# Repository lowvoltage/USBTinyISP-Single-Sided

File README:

Single-sided PCB version of the USBTinyISP v.2.0 AVR programmer

Original USBTinyISP v.2.0 design: LadyAda @ http://www.ladyada.net/make/usbtinyisp/
Original Single-sided PCB design: Jim Qode @ http://www.symbolengine.com/index.php/usbtinyisp-single-side-board-version/

Author: Dimitar Kovachev, http://lowvoltage.wordpress.com/

Released under the Creative Commons Attribution Share-Alike 3.0 license
http://creativecommons.org/licenses/by-sa/3.0/

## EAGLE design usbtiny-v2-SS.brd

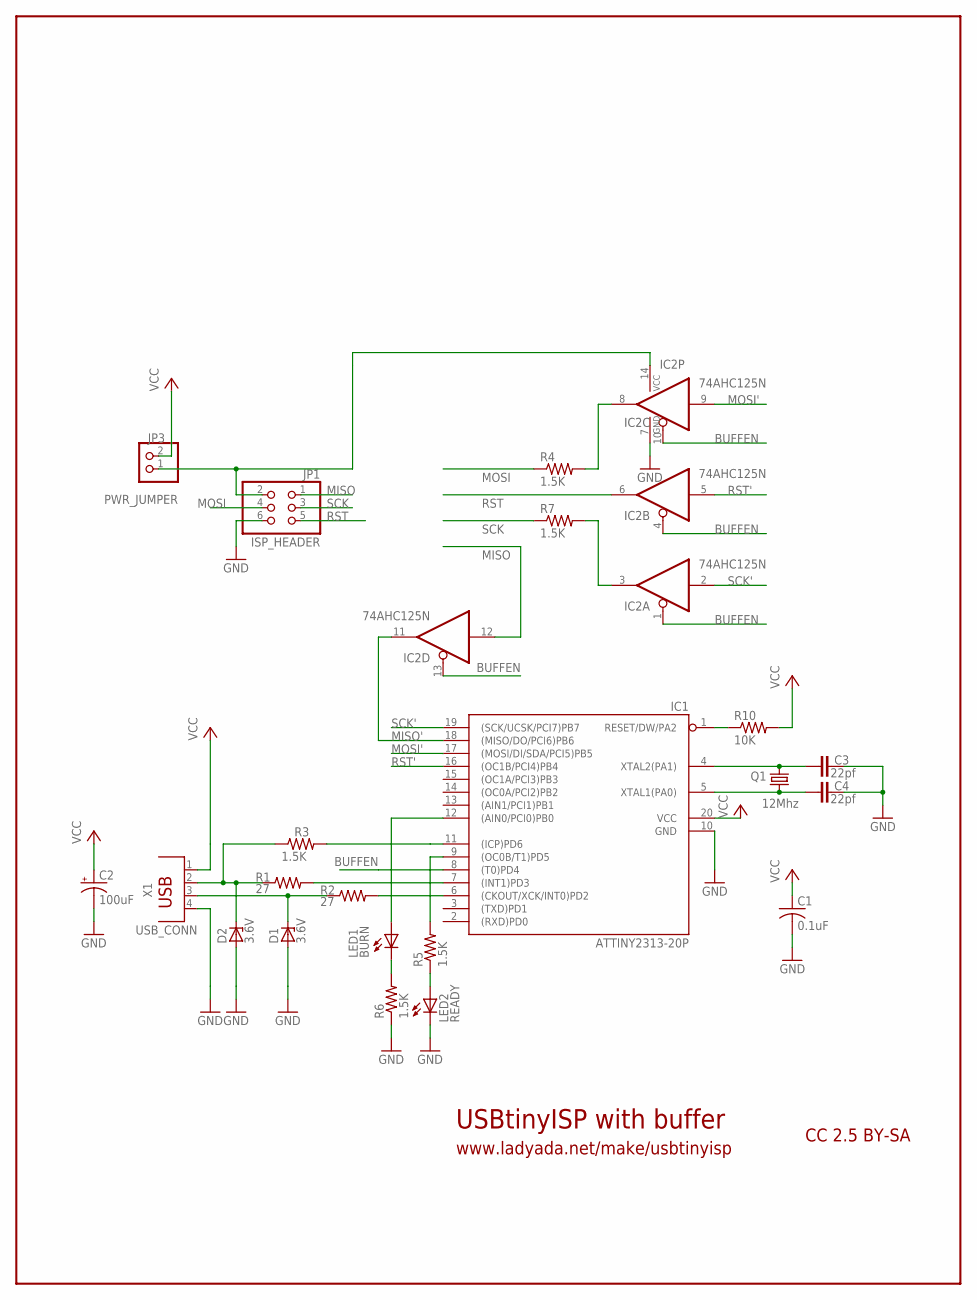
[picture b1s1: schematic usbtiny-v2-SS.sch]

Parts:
C1: 0.1uF; C025-025X050
C2: 100uF; E2,5-5
C3, C4: 22pf; C025-025X050
D1, D2: 3.6V; DO35Z10
IC1: ATTINY2313-20P; DIL20
IC2: 74AHC125N; DIL14
JP1: ISP_HEADER; 2X03
JP3: PWR_JUMPER; 1X02
LED1: BURN; LED3MM
LED2: READY; LED3MM
Q1: 12Mhz; HC49/S
R1, R2: 27; 0207/10
R3, R4, R7: 1.5K; 0207/10
R5, R6: 1.5K; 0207/2V
R10: 10K; 0207/10
X1: USB_CONN; PN61729

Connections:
BUFFEN: IC1.8 ((T0)PD4), IC2.1 (OE), IC2.4 (OE), IC2.10 (OE), IC2.13 (OE)
GND: C1.2, C2.-, C3.2, C4.2, D1.A, D2.A, IC1.10 (GND), IC2.7 (GND), JP1.6, LED2.K (C), R6.1, X1.4
MISO: IC2.12 (I), JP1.1
MISO': IC1.18 ((MISO/DO/PCI6)PB6), IC2.11 (O)
MOSI: JP1.4, R4.1
MOSI': IC1.17 ((MOSI/DI/SDA/PCI5)PB5), IC2.9 (I)
unnamed: D2.C, R1.1, R3.1, X1.2
unnamed: D1.C, R2.1, X1.3
unnamed: IC1.7 ((INT1)PD3), R1.2
unnamed: IC1.6 ((CKOUT/XCK/INT0)PD2), R2.2
unnamed: IC1.12 ((AIN0/PCI0)PB0), LED1.A
unnamed: LED1.K (C), R6.2
unnamed: IC1.1 (RESET/DW/PA2), R10.1
unnamed: IC1.9 ((OC0B/T1)PD5), R5.2
unnamed: LED2.A, R5.1
unnamed: IC2.3 (O), R7.2
unnamed: IC2.8 (O), R4.2
unnamed: IC1.11 ((ICP)PD6), R3.2
unnamed: C3.1, IC1.4 (XTAL2(PA1)), Q1.2
unnamed: C4.1, IC1.5 (XTAL1(PA0)), Q1.1
RST: IC2.6 (O), JP1.5
RST': IC1.16 ((OC1B/PCI4)PB4), IC2.5 (I)
SCK: JP1.3, R7.1
SCK': IC1.19 ((SCK/UCSK/PCI7)PB7), IC2.2 (I)
VCC: C1.1, C2.+, IC1.20 (VCC), JP3.2, R10.2, X1.1
VCC_REMOTE: IC2.14 (VCC), JP1.2, JP3.1

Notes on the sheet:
USBtinyISP with buffer
www.ladyada.net/make/usbtinyisp
CC 2.5 BY-SA

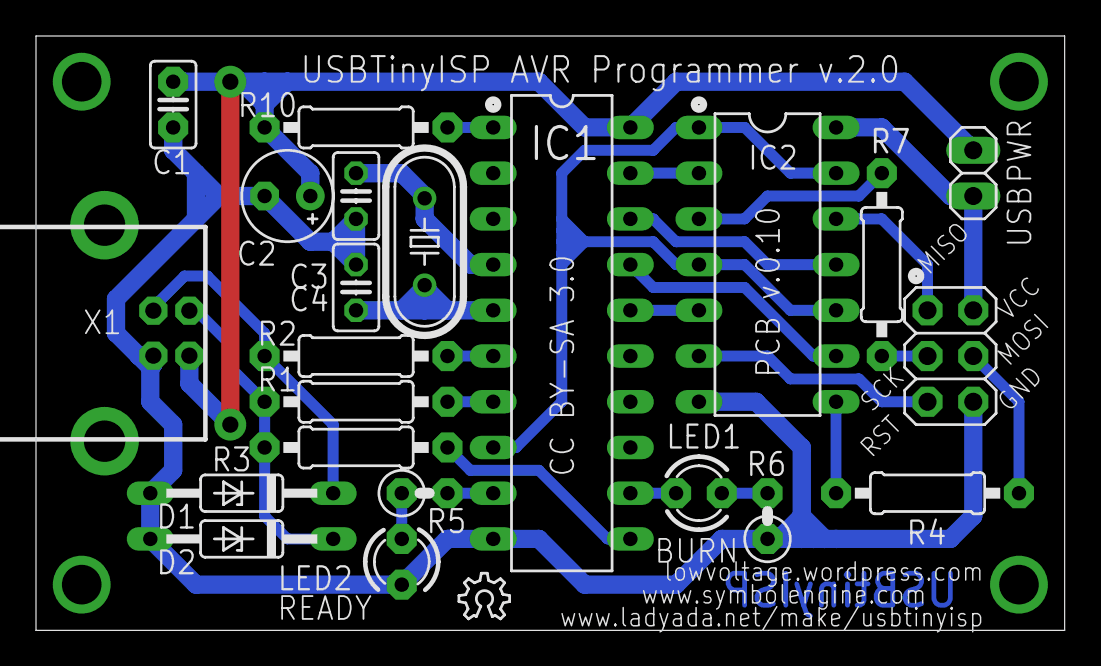
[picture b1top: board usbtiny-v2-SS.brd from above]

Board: 2 copper layers, 57.1 x 33.0 mm, 23 parts (0 on the bottom side), 26 nets.

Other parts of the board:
U$1: OSHW_6X100_NOTEXT

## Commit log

2012-06-28 Original version
2012-06-28 Version 0.01
2012-06-28 Removed spaces from filenames
2012-06-28 Version 0.02
2012-06-28 Version 0.03
2012-06-29 Version 0.04
2012-06-29 Version 0.05
2012-07-03 Version 0.06
2012-07-03 Version 0.07
2012-07-04 Schematic fixes, partial
2012-07-05 Version 0.08 - Final tweaks
2012-07-05 Added pin-1 dots
2012-07-05 Version 0.09 - Vector fonts
2012-07-06 Add PCB version. Optimize wires. Fix jumper clearance
2012-07-06 Version 0.10
2012-07-06 Metric drill holes
2012-07-07 Enabled tDocu layer
2012-07-07 Fixed board dimensions
2012-07-07 Updated initial PCB image
2012-07-07 Added .gitignore & README
2012-07-07 Proper README

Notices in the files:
usbtiny-v2-SS.brd:
CC BY-SA 3.0
